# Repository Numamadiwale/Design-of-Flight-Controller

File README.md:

# Design-of-Flight-Controller
Design of a flight controllern using KiCad Ver 9.0
the Design was made using the below list of components for a Drone : 

3D view of the final design :

still optimization is needed for minimization of the board size, No DRC errors recorded. Caution is to be exercised and further validation required.

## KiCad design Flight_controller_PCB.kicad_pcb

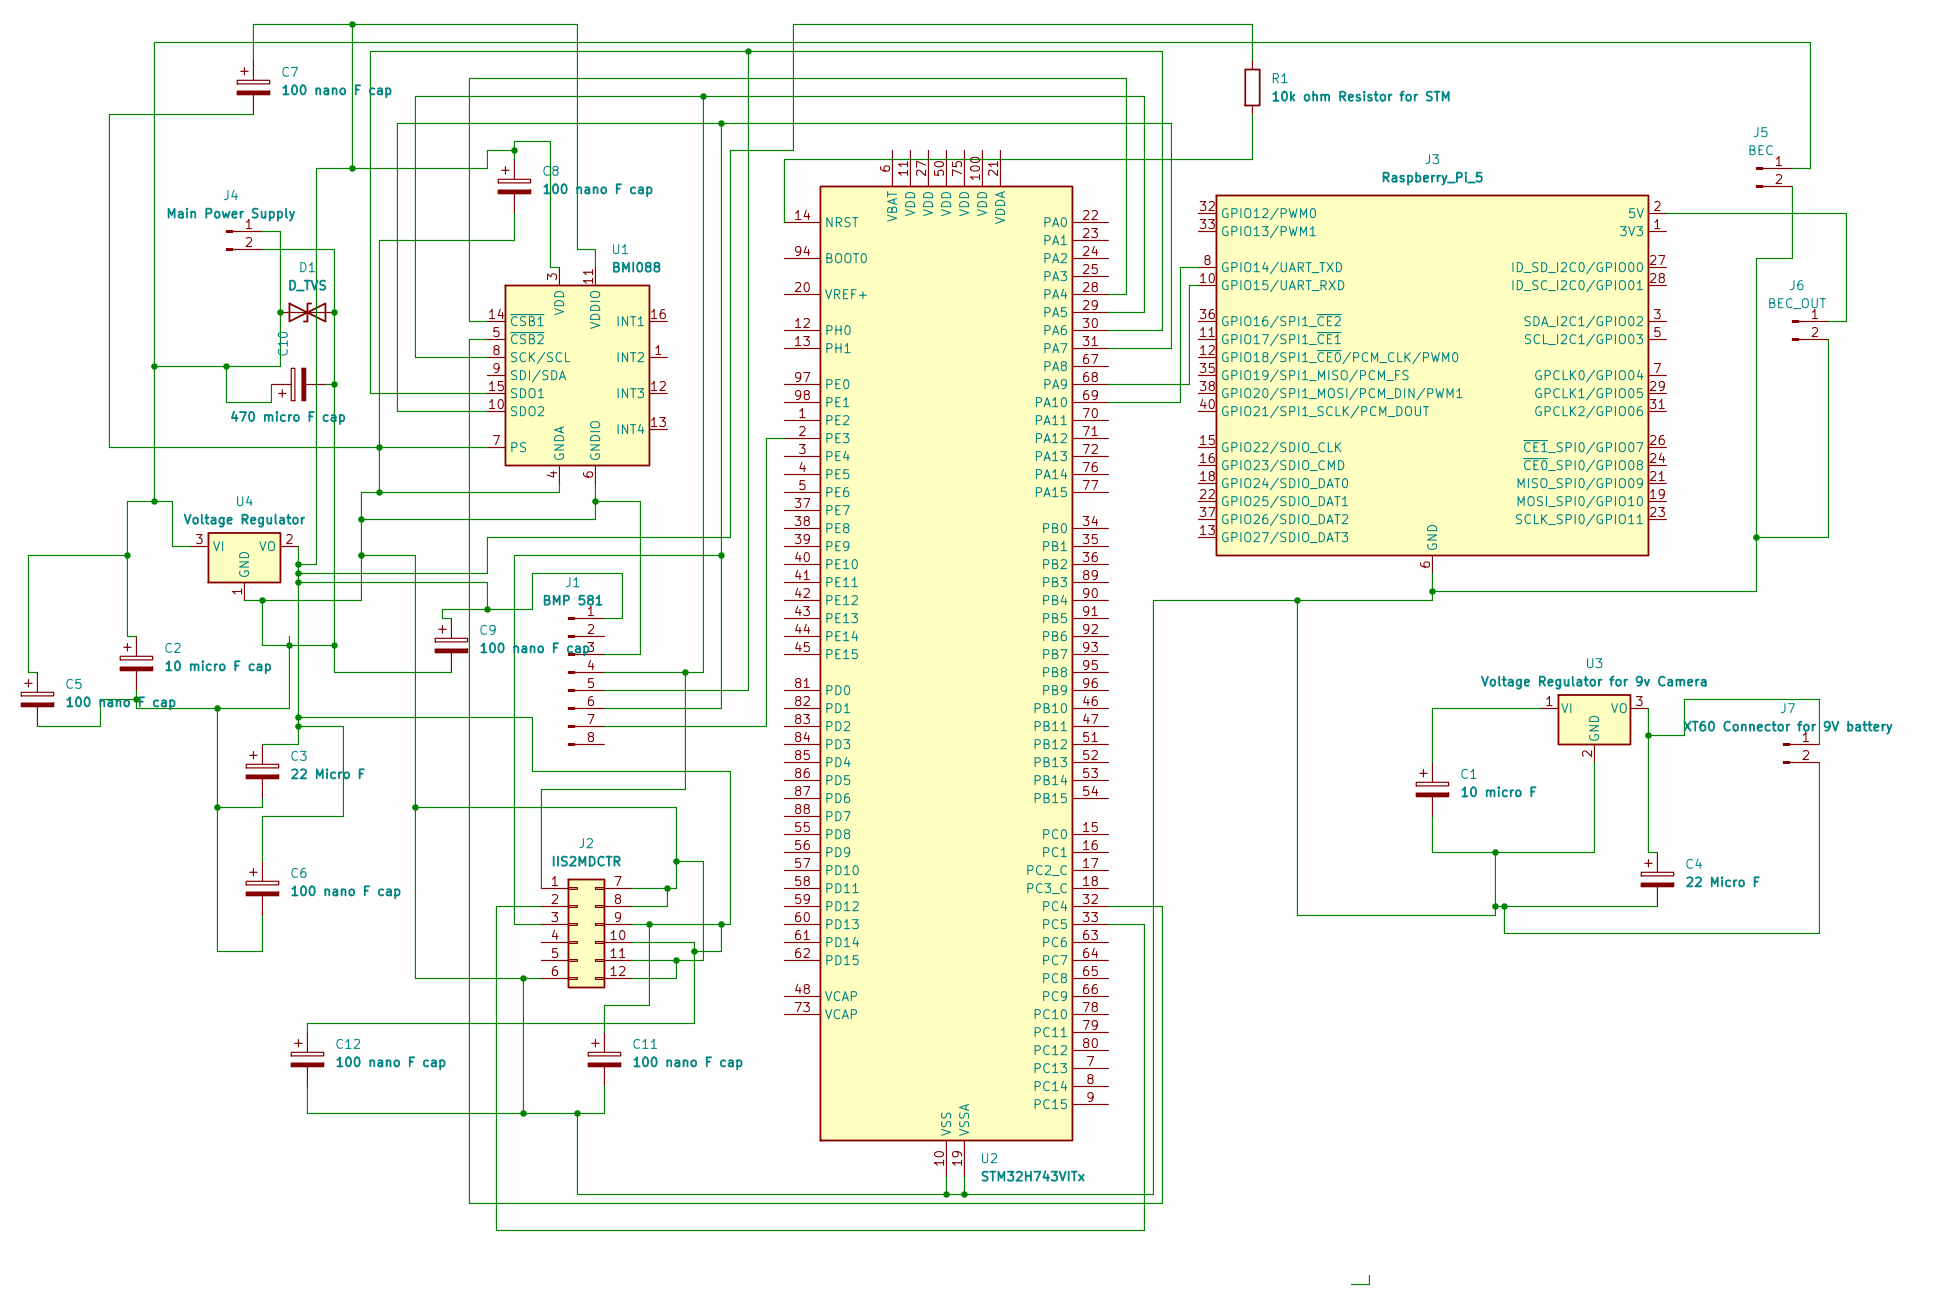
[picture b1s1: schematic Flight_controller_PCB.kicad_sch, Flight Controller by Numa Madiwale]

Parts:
C1: 10 micro F; CP_Elec_3x5.3
C2: 10 micro F cap; CP_Elec_3x5.3
C3, C4: 22 Micro F; CP_Elec_3x5.3
C5, C6, C7, C8, C9, C11, C12: 100 nano F cap; C_0805_2012Metric_Pad1.18x1.45mm_HandSolder
C10: 470 micro F cap; CP_Radial_D10.0mm_P5.00mm
D1: D_TVS; D_SMA_Handsoldering
J1: BMP 581; PinHeader_1x08_P2.54mm_Vertical
J2: IIS2MDCTR; Kionix_LGA-12_2x2mm_P0.5mm_LayoutBorder2x4y
J3: Raspberry_Pi_5; PinHeader_2x20_P2.54mm_Vertical
J4: Main Power Supply; AMASS_XT60-M_1x02_P7.20mm_Vertical
J5: BEC; PinHeader_1x02_P2.54mm_Vertical
J6: BEC_OUT; PinHeader_1x02_P2.54mm_Vertical
J7: XT60 Connector for 9V battery; AMASS_XT60-M_1x02_P7.20mm_Vertical
R1: 10k ohm Resistor for STM; R_0805_2012Metric_Pad1.20x1.40mm_HandSolder
U1: BMI088; Bosch_LGA-16_4.5x3mm_P0.5mm_LayoutBorder7x1y_ClockwisePinNu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
U2: STM32H743VITx; LQFP-100_14x14mm_P0.5mm
U3: Voltage Regulator for 9v Camera; TO-220-3_Vertical
U4: Voltage Regulator; SOT-223-3_TabPin2

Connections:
unnamed: C2.1, C5.1, C10.1, D1.1 (A1), J4.1 (V_BAT), J5.1, U4.3 (VI)
unnamed: C1.2, C2.2, C3.2, C4.2, C5.2, C6.2, C7.2, C8.2, C9.2, C10.2, C11.2, C12.2, D1.2 (A2), J1.3, J2.6, J2.7, J2.8, J2.11, J2.12, J3.6 (GND), J3.9 (GND), J3.14 (GND), J3.20 (GND), J3.25 (GND), J3.30 (GND), J3.34 (GND), J3.39 (GND), J4.2 (GND), J5.2, J6.2, J7.2, U1.2 (GNDA), U1.4 (GNDA), U1.6 (GNDIO), U1.7 (PS), U2.10 (VSS), U2.19 (VSSA), U2.26 (VSS), U2.49 (VSS), U2.74 (VSS), U2.99 (VSS), U3.2 (GND), U4.1 (GND)
unnamed: C3.1, C6.1, C7.1, C8.1, C9.1, C11.1, C12.1, J1.1, J2.9, J2.10, R1.1, U1.3 (VDD), U1.11 (VDDIO), U4.2 (VO)
unnamed: J1.4, J2.1, U1.8 (SCK/SCL), U2.29 (PA5)
unnamed: J1.5, U1.15 (SDO1), U2.30 (PA6)
unnamed: J1.6, J2.3, U1.10 (SDO2), U2.31 (PA7)
unnamed: J1.7, U2.2 (PE3)
unnamed: J2.2, U2.33 (PC5)
unnamed: J3.1 (3V3), J3.17 (3V3)
unnamed: J3.8 (GPIO14/UART_TXD), U2.69 (PA10)
unnamed: J3.10 (GPIO15/UART_RXD), U2.68 (PA9)
unnamed: J3.2 (5V), J3.4 (5V), J6.1
unnamed: C4.1, J7.1, U3.3 (VO)
unnamed: U1.14 (~CSB1), U2.28 (PA4)
unnamed: U1.5 (~CSB2), U2.32 (PC4)
unnamed: R1.2, U2.14 (NRST)
unnamed: C1.1, U3.1 (VI)

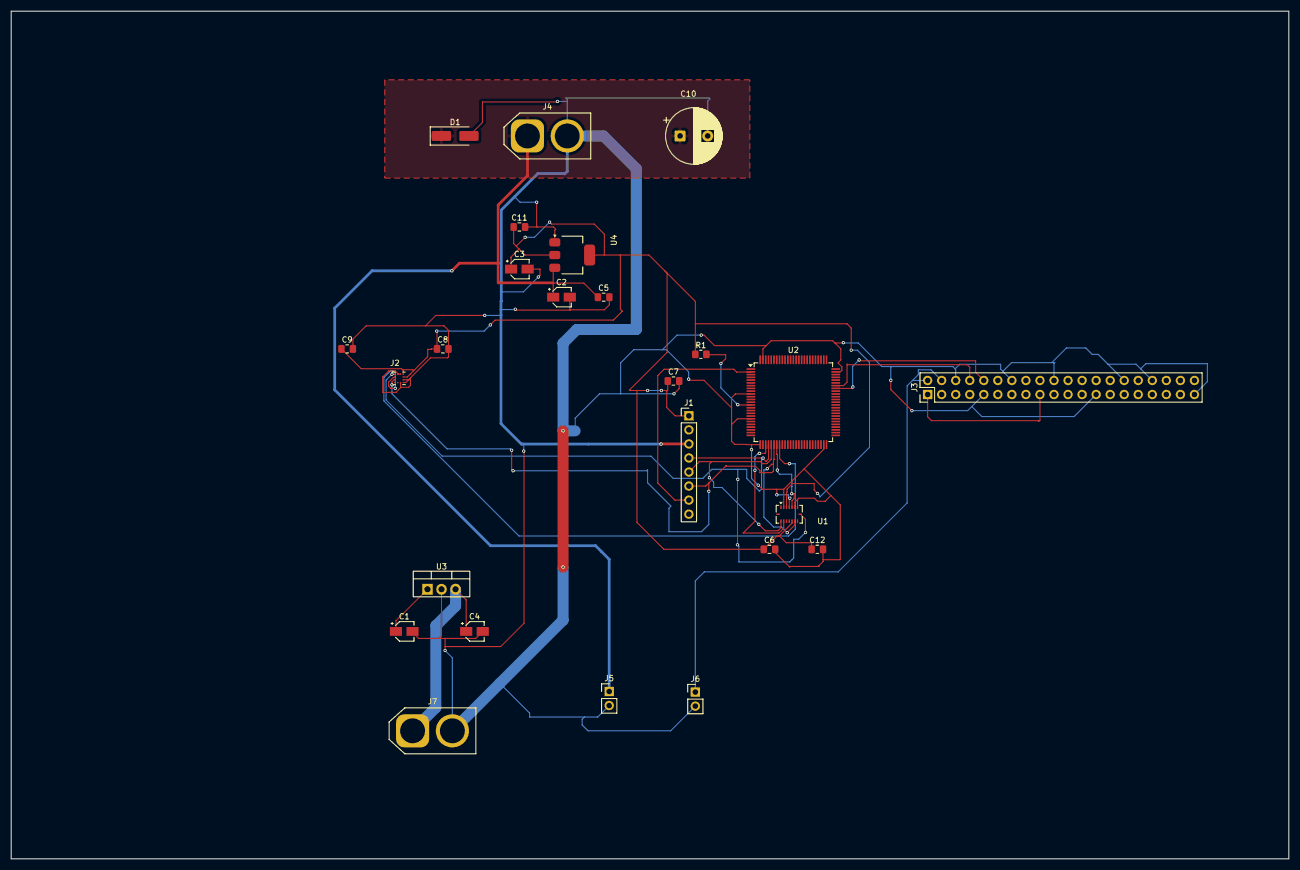
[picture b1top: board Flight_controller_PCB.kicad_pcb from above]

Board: 2 copper layers, 231.1 x 153.3 mm, 25 parts (0 on the bottom side), 17 nets.
